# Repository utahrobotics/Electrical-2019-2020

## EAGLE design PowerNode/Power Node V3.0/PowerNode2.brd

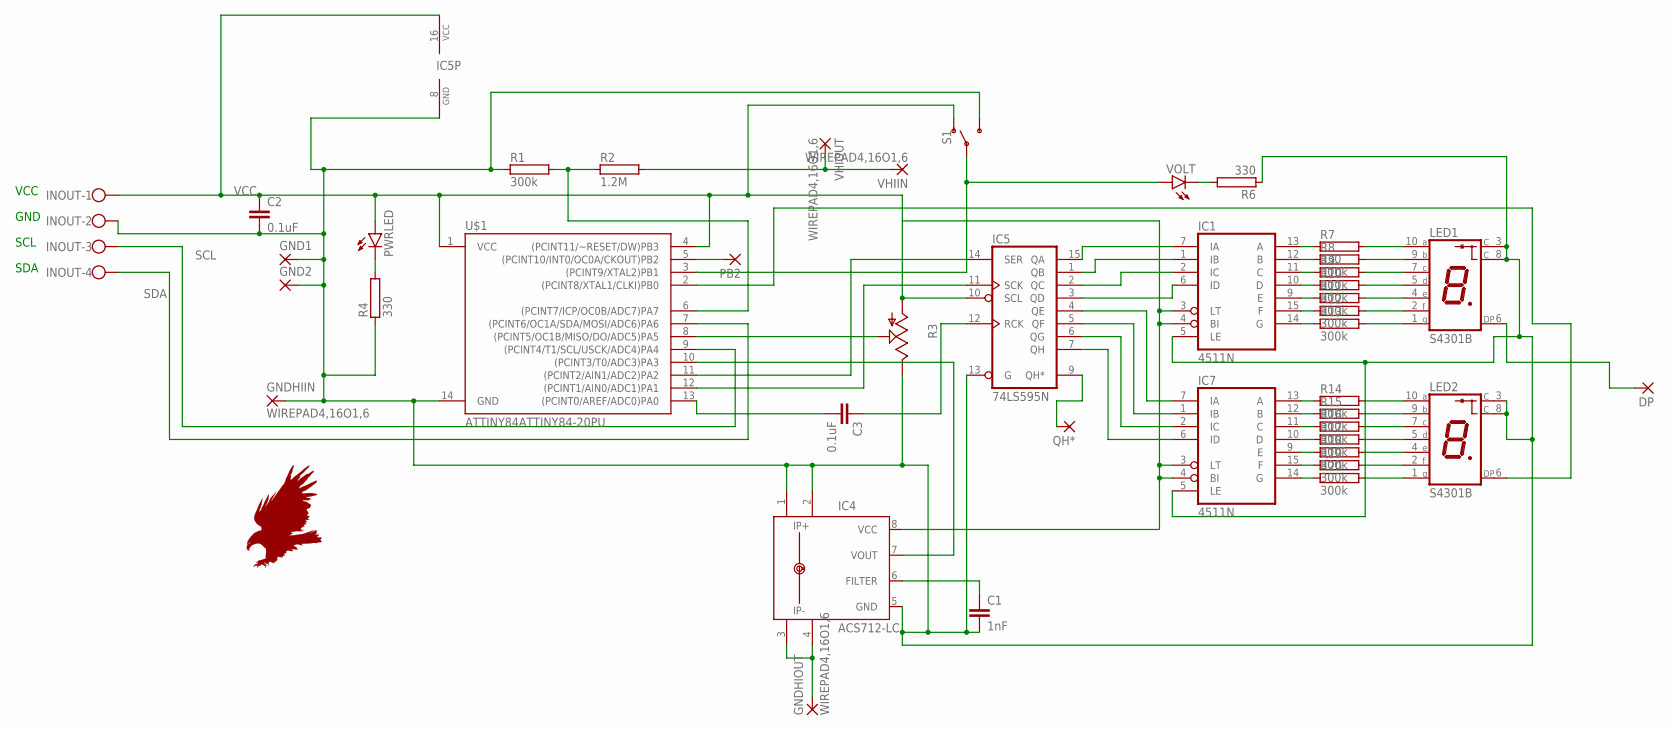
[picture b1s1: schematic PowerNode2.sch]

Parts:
C1: 1nF; C5B3
C2, C3: 0.1uF; C5B3
DP: 2,54/0,9
GND1, GND2: 2,15/1,0
GNDHIIN: WIREPAD4,16O1,6; 4,16O1,6
GNDHIOUT: WIREPAD4,16O1,6; 4,16O1,6
IC1, IC7: 4511N; DIL16
IC4: ACS712-LC; SOIC8
IC5: 74LS595N; DIL16
INOUT: W237-4
LED1, LED2: S4301B
PB2: 2,54/0,9
PWRLED: LED5MM
QH*: 2,54/0,9
R1, R8, R9, R10, R11, R12, R13, R14, R15, R16, R17, R18, R19, R20: 300k; KH206-8R
R2: 1.2M; KH206-8R
R3: TRIM_US-B25P; B25P
R4, R6, R7: 330; KH206-8R
S1: SWITCH-SPDT-PTH-11.6X4.0MM; SWITCH_SPDT_PTH_11.6X4.0MM
U$1: ATTINY84ATTINY84-20PU; DIP14
VHIIN: WIREPAD4,16O1,6; 4,16O1,6
VHIOUT: WIREPAD4,16O1,6; 4,16O1,6
VOLT: LED5MM

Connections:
CALIB: R3.S, U$1.8 ((PCINT5/OC1B/MISO/DO/ADC5)PA5)
CURRIN: IC4.7 (VOUT), U$1.10 ((PCINT3/T0/ADC3)PA3)
DISPSEL: S1.2, U$1.3 ((PCINT9/XTAL2)PB1), VOLT.A
GND: C1.2, C2.2, GND1.1, GND2.1, GNDHIIN.1, IC1.5 (LE), IC4.1 (IP+), IC4.2 (IP+1), IC4.5 (GND), IC5.8 (GND), IC5.13 (G), IC7.5 (LE), INOUT.2, LED1.3 (C), LED1.8 (C), LED2.3 (C), LED2.8 (C), R1.1, R3.E, R4.1, R6.1, S1.3 (S), U$1.14 (GND)
GNDHIOUT: GNDHIOUT.1, IC4.3 (IP-), IC4.4 (IP-1)
unnamed: C1.1, IC4.6 (FILTER)
unnamed: IC5.14 (SER), U$1.11 ((PCINT2/AIN1/ADC2)PA2)
unnamed: IC1.13 (A), R7.1
unnamed: IC1.12 (B), R8.1
unnamed: IC1.11 (C), R9.1
unnamed: IC1.10 (D), R10.1
unnamed: IC1.9 (E), R11.1
unnamed: IC1.15 (F), R12.1
unnamed: IC1.14 (G), R13.1
unnamed: IC1.7 (IA), IC5.15 (QA)
unnamed: IC1.1 (IB), IC5.1 (QB)
unnamed: IC1.2 (IC), IC5.2 (QC)
unnamed: IC1.6 (ID), IC5.3 (QD)
unnamed: LED1.10 (A), R7.2
unnamed: LED1.9 (B), R8.2
unnamed: LED1.7 (C), R9.2
unnamed: LED1.5 (D), R10.2
unnamed: LED1.4 (E), R11.2
unnamed: LED1.2 (F), R12.2
unnamed: LED1.1 (G), R13.2
unnamed: IC7.13 (A), R14.1
unnamed: IC7.12 (B), R15.1
unnamed: IC7.11 (C), R16.1
unnamed: IC7.10 (D), R17.1
unnamed: IC7.9 (E), R18.1
unnamed: IC5.11 (SCK), U$1.12 ((PCINT1/AIN0/ADC1)PA1)
unnamed: C3.1, IC5.12 (RCK)
unnamed: C3.2, U$1.13 ((PCINT0/AREF/ADC0)PA0)
unnamed: LED2.6 (DP), U$1.2 ((PCINT8/XTAL1/CLKI)PB0)
unnamed: PB2.1, U$1.5 ((PCINT10/INT0/OC0A/CKOUT)PB2)
unnamed: PWRLED.K (C), R4.2
unnamed: R6.2, VOLT.K (C)
unnamed: IC5.9 (QH*), QH*.1
unnamed: IC7.15 (F), R19.1
unnamed: DP.1, LED1.6 (DP)
unnamed: IC7.14 (G), R20.1
unnamed: LED2.10 (A), R14.2
unnamed: LED2.9 (B), R15.2
unnamed: LED2.7 (C), R16.2
unnamed: LED2.5 (D), R17.2
unnamed: LED2.4 (E), R18.2
unnamed: LED2.2 (F), R19.2
unnamed: LED2.1 (G), R20.2
unnamed: IC5.4 (QE), IC7.7 (IA)
unnamed: IC5.5 (QF), IC7.1 (IB)
unnamed: IC5.6 (QG), IC7.2 (IC)
unnamed: IC5.7 (QH), IC7.6 (ID)
SCL: INOUT.3, U$1.9 ((PCINT4/T1/SCL/USCK/ADC4)PA4)
SDA: INOUT.4, U$1.7 ((PCINT6/OC1A/SDA/MOSI/ADC6)PA6)
VCC: C2.1, IC1.3 (LT), IC1.4 (BI), IC4.8 (VCC), IC5.10 (SCL), IC5.16 (VCC), IC7.3 (LT), IC7.4 (BI), INOUT.1, PWRLED.A, R3.A, S1.1 (O), U$1.1 (VCC), U$1.4 ((PCINT11/~RESET/DW)PB3)
VDD: IC1.16 (VDD), IC7.16 (VDD)
VHI: R2.2, VHIIN.1, VHIOUT.1
VHIOUT: R1.2, R2.1, U$1.6 ((PCINT7/ICP/OC0B/ADC7)PA7)
VSS: IC1.8 (VSS), IC7.8 (VSS)

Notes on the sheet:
SCL
GND
VCC
SDA

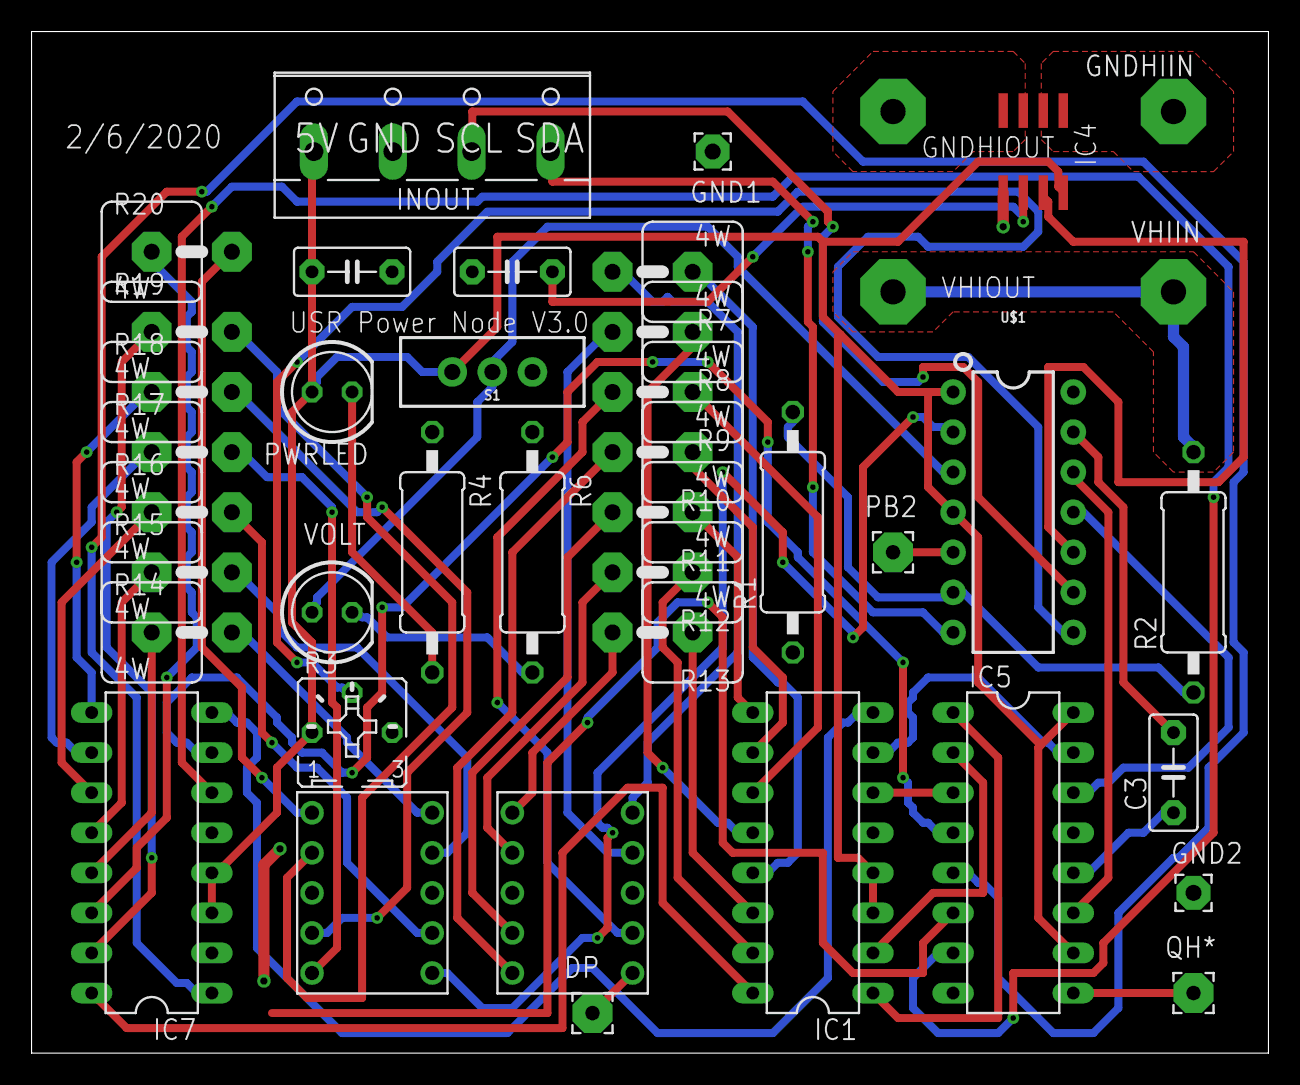
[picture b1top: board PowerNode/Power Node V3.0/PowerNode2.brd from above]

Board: 2 copper layers, 78.4 x 64.8 mm, 42 parts (0 on the bottom side), 58 nets.

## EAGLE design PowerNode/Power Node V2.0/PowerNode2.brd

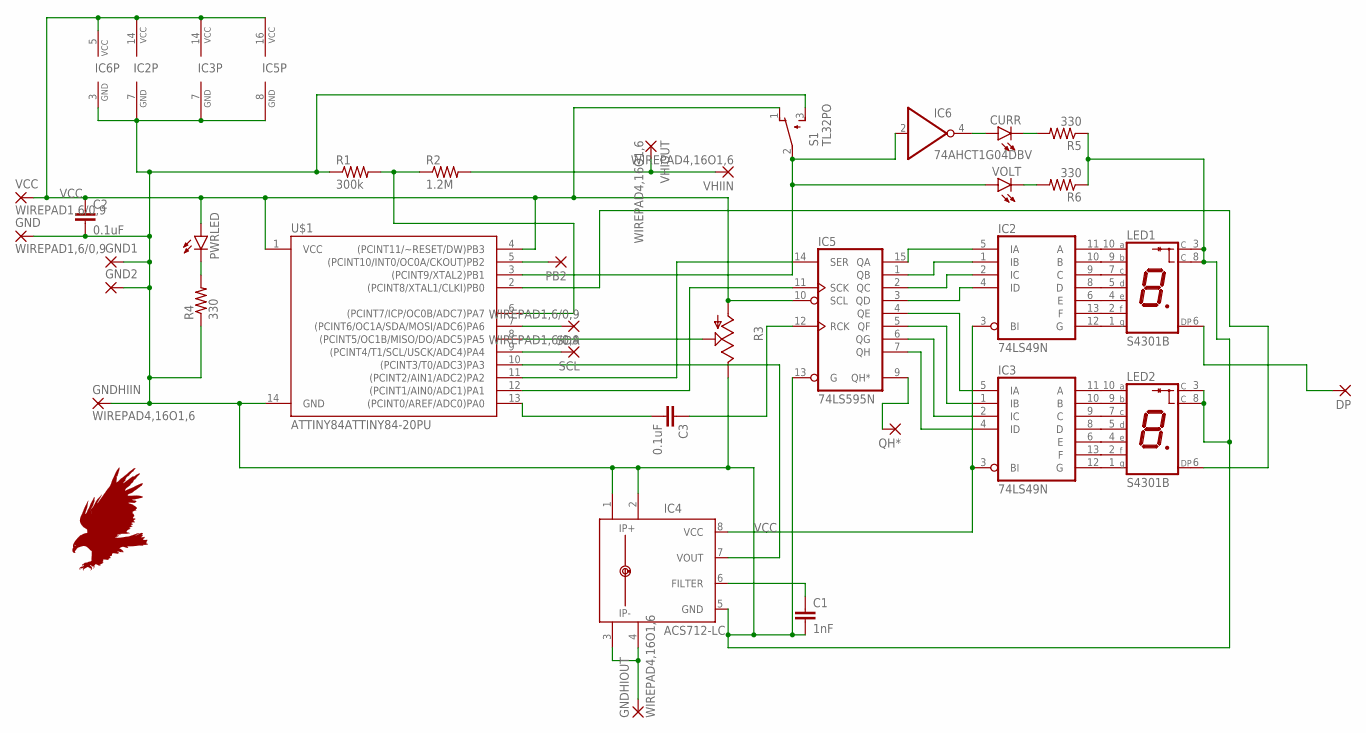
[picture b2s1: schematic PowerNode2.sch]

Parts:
C1: 1nF; C5B3
C2, C3: 0.1uF; C5B3
CURR: LED5MM
DP: 2,54/0,9
GND: WIREPAD1,6/0,9; 1,6/0,9
GND1, GND2: 2,15/1,0
GNDHIIN: WIREPAD4,16O1,6; 4,16O1,6
GNDHIOUT: WIREPAD4,16O1,6; 4,16O1,6
IC2, IC3: 74LS49N; DIL14
IC4: ACS712-LC; SOIC8
IC5: 74LS595N; DIL16
IC6: 74AHCT1G04DBV; SOT23-5
LED1, LED2: S4301B
PB2: 2,54/0,9
PWRLED: LED5MM
QH*: 2,54/0,9
R1: 300k; 0411/15
R2: 1.2M; 0411/15
R3: TRIM_US-B25P; B25P
R4, R5, R6: 330; 0411/15
S1: TL32PO; TL3XPO
SCL: WIREPAD1,6/0,9; 1,6/0,9
SDA: WIREPAD1,6/0,9; 1,6/0,9
U$1: ATTINY84ATTINY84-20PU; DIP14
VCC: WIREPAD1,6/0,9; 1,6/0,9
VHIIN: WIREPAD4,16O1,6; 4,16O1,6
VHIOUT: WIREPAD4,16O1,6; 4,16O1,6
VOLT: LED5MM

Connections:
CALIB: R3.S, U$1.8 ((PCINT5/OC1B/MISO/DO/ADC5)PA5)
CURRIN: IC4.7 (VOUT), U$1.10 ((PCINT3/T0/ADC3)PA3)
DISPSEL: IC6.2 (I), S1.2, U$1.3 ((PCINT9/XTAL2)PB1), VOLT.A
GND: C1.2, C2.2, GND.1, GND1.1, GND2.1, GNDHIIN.1, IC2.7 (GND), IC3.7 (GND), IC4.1 (IP+), IC4.2 (IP+1), IC4.5 (GND), IC5.8 (GND), IC5.13 (G), IC6.3 (GND), LED1.3 (C), LED1.8 (C), LED2.3 (C), LED2.8 (C), R1.1, R3.E, R4.1, R5.1, R6.1, S1.3 (S), U$1.14 (GND)
GNDHIOUT: GNDHIOUT.1, IC4.3 (IP-), IC4.4 (IP-1)
unnamed: C1.1, IC4.6 (FILTER)
unnamed: IC5.14 (SER), U$1.11 ((PCINT2/AIN1/ADC2)PA2)
unnamed: IC2.6 (E), LED1.4 (E)
unnamed: SCL.1, U$1.9 ((PCINT4/T1/SCL/USCK/ADC4)PA4)
unnamed: SDA.1, U$1.7 ((PCINT6/OC1A/SDA/MOSI/ADC6)PA6)
unnamed: IC2.8 (D), LED1.5 (D)
unnamed: IC2.9 (C), LED1.7 (C)
unnamed: IC2.10 (B), LED1.9 (B)
unnamed: IC2.11 (A), LED1.10 (A)
unnamed: IC2.12 (G), LED1.1 (G)
unnamed: IC2.13 (F), LED1.2 (F)
unnamed: IC3.13 (F), LED2.2 (F)
unnamed: IC3.8 (D), LED2.5 (D)
unnamed: IC3.10 (B), LED2.9 (B)
unnamed: IC3.11 (A), LED2.10 (A)
unnamed: IC3.9 (C), LED2.7 (C)
unnamed: IC3.6 (E), LED2.4 (E)
unnamed: IC3.12 (G), LED2.1 (G)
unnamed: IC2.5 (IA), IC5.15 (QA)
unnamed: IC2.1 (IB), IC5.1 (QB)
unnamed: IC2.2 (IC), IC5.2 (QC)
unnamed: IC2.4 (ID), IC5.3 (QD)
unnamed: IC3.5 (IA), IC5.4 (QE)
unnamed: IC3.1 (IB), IC5.5 (QF)
unnamed: IC3.2 (IC), IC5.6 (QG)
unnamed: IC3.4 (ID), IC5.7 (QH)
unnamed: IC5.11 (SCK), U$1.12 ((PCINT1/AIN0/ADC1)PA1)
unnamed: C3.1, IC5.12 (RCK)
unnamed: C3.2, U$1.13 ((PCINT0/AREF/ADC0)PA0)
unnamed: LED2.6 (DP), U$1.2 ((PCINT8/XTAL1/CLKI)PB0)
unnamed: PB2.1, U$1.5 ((PCINT10/INT0/OC0A/CKOUT)PB2)
unnamed: PWRLED.K (C), R4.2
unnamed: CURR.K (C), R5.2
unnamed: R6.2, VOLT.K (C)
unnamed: CURR.A, IC6.4 (O)
unnamed: IC5.9 (QH*), QH*.1
unnamed: DP.1, LED1.6 (DP)
VCC: C2.1, IC2.3 (BI), IC2.14 (VCC), IC3.3 (BI), IC3.14 (VCC), IC4.8 (VCC), IC5.10 (SCL), IC5.16 (VCC), IC6.5 (VCC), PWRLED.A, R3.A, S1.1 (O), U$1.1 (VCC), U$1.4 ((PCINT11/~RESET/DW)PB3), VCC.1
VHI: R2.2, VHIIN.1, VHIOUT.1
VHIOUT: R1.2, R2.1, U$1.6 ((PCINT7/ICP/OC0B/ADC7)PA7)

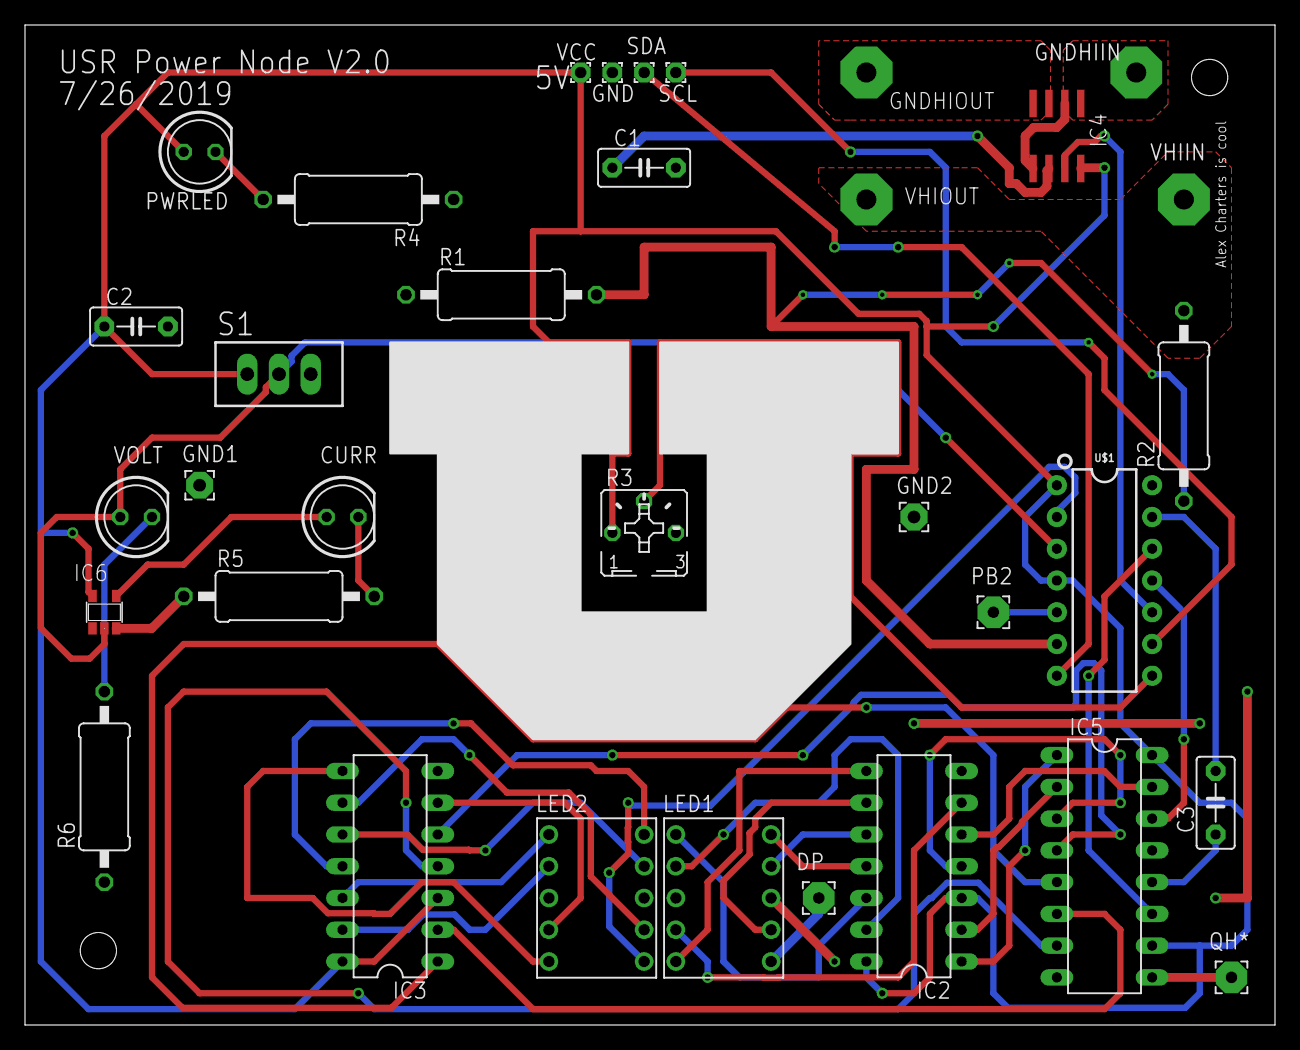
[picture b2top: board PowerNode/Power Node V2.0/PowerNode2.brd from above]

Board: 2 copper layers, 100.0 x 80.0 mm, 34 parts (0 on the bottom side), 45 nets.

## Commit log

2019-10-01 added incomplete master schematic
2019-10-22 most up to date
2019-10-22 added snip
2019-10-22 pictures
2019-12-03 updated master schematic
2019-12-03 oops ignore last commit lmao XD I wanna die skeet skdefs
2020-01-03 added powernode slave code (not tested) and pinout diagram for attiny 84
2020-01-15 picture
2020-01-16 added electrical solidworks layout
2020-01-17 added eagle files
2020-01-17 Project cleanup
2020-01-17 Moved power node files to KiCAD
2020-01-17 Moved power node files to KiCAD
    Also removed old capture and added .gitignore
2020-01-17 Fixed a library renaming issue
2020-01-18 Added generated file for power node
2020-01-18 Added master schematic KiCAD files
2020-01-18 Added power node to master schematic
2020-01-18 Added motor controllers to master schematic
2020-01-18 Added agg-kicad library
2020-01-18 added more electrical components
2020-01-18 Added duplicate required motor controllers to master schematic
2020-01-18 Changed schematic paper size to A2 for more space
2020-01-18 Updated Roboclaw
2020-01-18 Added brushed motors to master schematic
2020-01-18 Added stepper motors to MS and small changes to Pololu3730.sch
2020-01-21 started wiring stuff
2020-01-21 added dependencies
2020-01-22 Added 3 more power nodes to master schematic
2020-01-22 Added IMU interface board files
2020-01-22 Annotated and updated schematic
2020-01-22 Added the real IMU interface board files
2020-01-22 Cleaned up the real IMU interface board schematic
2020-01-22 Added emergency stop button and cleaned up IMU interface board
2020-01-22 Added IMU interface board hierarchical pins and ODrive USB marker to MS
2020-01-26 Added Teensy 4 code
2020-02-04 added shift reg test
2020-02-05 Updated to schematic version 5 (sorted components)
2020-02-05 Added Jetson and updated drive motors (removed ODrive)
2020-02-07 .gitignore update
2020-02-07 Updated ground and IMU connections and added logic converter
2020-02-07 IMU Interface Board updates and improvements and general cleanup
2020-02-07 Updated IMU Interface Board libraries
2020-02-07 Cleanup .bck and fp-info-cache files
2020-02-08 working on powernode V3.0
2020-02-22 Added 2 new error signals to Teensy code
2020-02-22 Fixed IMU data scaling
2020-02-28 Removed old power node files and cleaned up master schematic
2020-02-28 PN3: schematic cleanup and moved logic to its own sheet
2020-02-28 PN3: added DPDT switch symbol and 3D switch models
2020-02-28 Power node 3.0 fixes, updates, and improvements
2020-02-28 Updated PN3 schematic to newer version and added/updated CL and PD resistors
2020-02-28 PN3: updated board and footprints
2020-02-28 PN3: updated PCB and added protective capacitors to VMEAS
2020-02-28 PN3: added spice models for switch, LEDs, LTS-4301P and ACS712
2020-02-28 PN3: removed R2 and replaced with a switched voltage divider
2020-02-28 PN3: changed resistors to use SMD footprints
2020-02-28 Removed BJTs and connected VMEAS directly
2020-02-28 PN3: added voltage follower to VMEAS and removed zener diode
2020-02-28 PN3: Improved ACS712 model, added simulation noise, and swapped IP+ and IP- order
2020-02-28 PN3 simulation fixes and updates (added models)
2020-02-28 PN3: datasheet update
2020-02-28 Remapped PN3 footprints
2020-02-28 PN3: Fixed potentiometer footprint mappings
2020-02-28 PN3: added ATTiny84 spice model and BJT models file
2020-02-28 PN3: added logic schematic (oops) and protective diode/capacitors for ATTiny inputs
2020-02-28 Added PN3 spice models for screw terminal and CD4511B plus generating script
2020-02-28 Remapped some components in power node v3.0
2020-02-28 Cleaned up PN3 10k resistors
2020-02-28 PN3: small simulation improvements
2020-02-28 PN3: removed 100uF capacitor and cleaned up some things
2020-02-28 PN3: added pull-down resistors for DP1 and QH*1
2020-02-28 PN3: corrected connection sorting
2020-02-28 PN3: updated footprints and 3D models
2020-02-28 PN3: Fixes for SPICE simulation
2020-02-28 Cleanup and connected logic ground to GND in PN3 schematic
2020-02-28 PN3: added labels, input voltage, and fixes to help with simulation
2020-02-28 PN3: board update/corrections
2020-02-28 Imported files to KiCAD
2020-03-03 PN3: small changes to DPDT symbol
2020-03-04 PN3: reannotated schematic and updated board
2020-03-04 PN3: connected 5V indicator to PB2 and other small changes
2020-03-04 PN3: improvements for simulation (added workbook)
2020-03-05 PN3: added better 3D switch models
2020-03-05 PN3: removed extra low-pass filter from IMEAS
2020-03-06 PN3: changed LEDs to SMD and VOLT1 to bi-color, other small changes
2020-03-07 PN3: changed to resistor networks from drivers and footprint/model cleanup
2020-03-07 PN3: added image and labels for prototyping
2020-03-09 IMU_Interface signal pin change
2020-03-09 Added serial printing for debug to IMU_Interface
2020-03-09 Updates from master
2020-03-09 Added new topic for raw data
2020-03-11 Sign error fixes and optimization using ldexp
2020-03-11 Fixes and optimizations to IMU_Interface code
2020-03-11 Cleaned up IMU_Interface code and added comments
2020-03-25 PN3: more routing changes
2020-03-25 PN3: Started routing and made appropriate adjustments
    One noteworthy adjustment was switching the VMEAS and VPOT pins
    on the ATTiny. The slave code was also updated.
2020-03-25 PN3: finished routing
2020-03-25 PN3: added models accidentally left out
2020-03-25 PN3: updated ATTiny code to use VPASS signal
2020-03-25 PN3: added logos and cleaned up connections
2020-03-25 PN3: updated 3D switch models
2020-03-25 PN3: created 3D models and small board changes
2020-03-25 PN3: added BOM and small board changes
2020-03-25 PN3: changed bi-color LED for separate LEDs and switches
2020-03-25 PN3: board fill and 3D model update
2020-03-26 PN3: updated switch board models
2020-03-27 PN3: made HI pads cover both sides
2020-03-27 PN3: board updates (placeholder)
2020-03-28 PN3: board reroute for higher current
2020-03-28 PN3: 3D model update
2020-03-29 Moved resistor networks out from under the seven segment displays to avoid soldering woes. Also, moved right-angle measure select switch to the side of the board for easy access.
2020-03-30 PN3: routing changes to reduce number of tracks and inductance
2021-10-23 Fixed a possible issue causing the clock interrupt to get detached much later than intended
2021-10-23 Simplified and fixed buffer logic
2021-10-23 Built updated code
2022-02-12 Updated for serial use
2022-02-12 Unbroke padding bit logic
2022-02-15 Still update timestamp when checksum fails
2022-02-16 Added more debug signals and small fix
2022-02-16 Added IMU initialization check and gravity offset
2022-02-16 Added init check for publishing and compiled
2022-02-17 Removed WFI to fix timing
2022-02-17 Small changes from master and for debug
2022-02-18 Added back bit reversal
2022-02-18 Better estimate for gravity in initialization
2022-02-18 Better gravity initialization and added normalized IMU message
2022-02-18 Added new publisher for normalized acceleration and fixed bit reversal
2022-02-18 Small changes and improvements
2022-02-19 Sync ROS timing and added spin timeout
2022-02-21 Added Twist and Transform publishers plus fixes and improvements
    - New publishers with improved gravity offset
    - IMU orientation in its frame of reference is considered zero
    - Rotation update now correctly uses IMU frame of reference
    - Other small fixes and readability improvements
2022-02-22 Updated for ROS debug with no IMU connected
2022-02-22 Added generated test data
2022-02-23 Timing fixes and added debug messages
2022-02-23 Debug improvements and small fix to init acceleration to gravity
2022-02-24 Simplified for USB debug
2022-02-24 Added separate error topic and improved time reporting
2022-02-25 Improved debug messages and publishing
2022-02-25 Added output signals for better debugging
2022-02-25 Added debug topic, improved publishing, and small fixes
2022-02-26 Improved error checking, correct DT when data is bad, and fixed gravity initialization
2022-02-26 Code cleanup
2022-03-05 Updated ROS library
2022-03-05 Updated to build correctly with rosserial setup
2022-03-05 Updates from master and small fixes/improvements
2022-03-05 Fixed issues in sending and receiving bits and added more debug printing
2022-03-05 No longer using reverse trapezoid rule
2022-03-05 Added more debug printing, no more reverse trapezoid rule, and fixes

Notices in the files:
parts and their libraries:
SparkFun-IC-Microcontroller: Licensing: Creative Commons ShareAlike 4.0 International - https://creativecommons.org/licenses/by-sa/4.0
